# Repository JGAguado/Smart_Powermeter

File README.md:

[![Documentation Status][documentation-shield]][documentation]
[![GitHub Release][releases-shield]][releases]
[![License][license-shield]](LICENSE)

[![Project Maintenance][maintenance-shield]][maintenance]
[![BuyMeCoffee][buymecoffee-shield]][buymecoffee]

# Smart Powermeter
The Smart Powermeter is powered by a ESP32-S2, allowing the measurement up to 6 CT clamps for reading electric current and real-time display on an 2.9" e-paper display.

Additionally, the 3rd version adds support to voltage measurement with up to 3 voltage measurement channels and independent adjustable gains. 

## Project tree

<li><a href="./Design/">Design</a></li>
<li><a href="./Documentation/">Documentation</a></li>

<li><a href="./README.md">README.md</a></li>

[documentation-shield]: https://readthedocs.org/projects/smart-powermeter/badge/?version=latest&style=for-the-badge
[documentation]: https://smart-powermeter.readthedocs.io/en/latest/

[releases-shield]: https://img.shields.io/github/release/JGAguado/Smart_Powermeter.svg?style=for-the-badge
[releases]: https://github.com/JGAguado/Smart_Powermeter/releases

[license-shield]: https://img.shields.io/badge/License-CC%20BY--NC--SA%204.0-lightgrey.svg?style=for-the-badge

[maintenance-shield]: https://img.shields.io/badge/maintainer-J.%20G.%20Aguado-blue.svg?style=for-the-badge
[maintenance]: https://github.com/JGAguado

[buymecoffee-shield]: https://img.shields.io/badge/buy%20me%20a%20coffee-support-yellow.svg?style=for-the-badge
[buymecoffee]: https://www.buymeacoffee.com/J.G.Aguado

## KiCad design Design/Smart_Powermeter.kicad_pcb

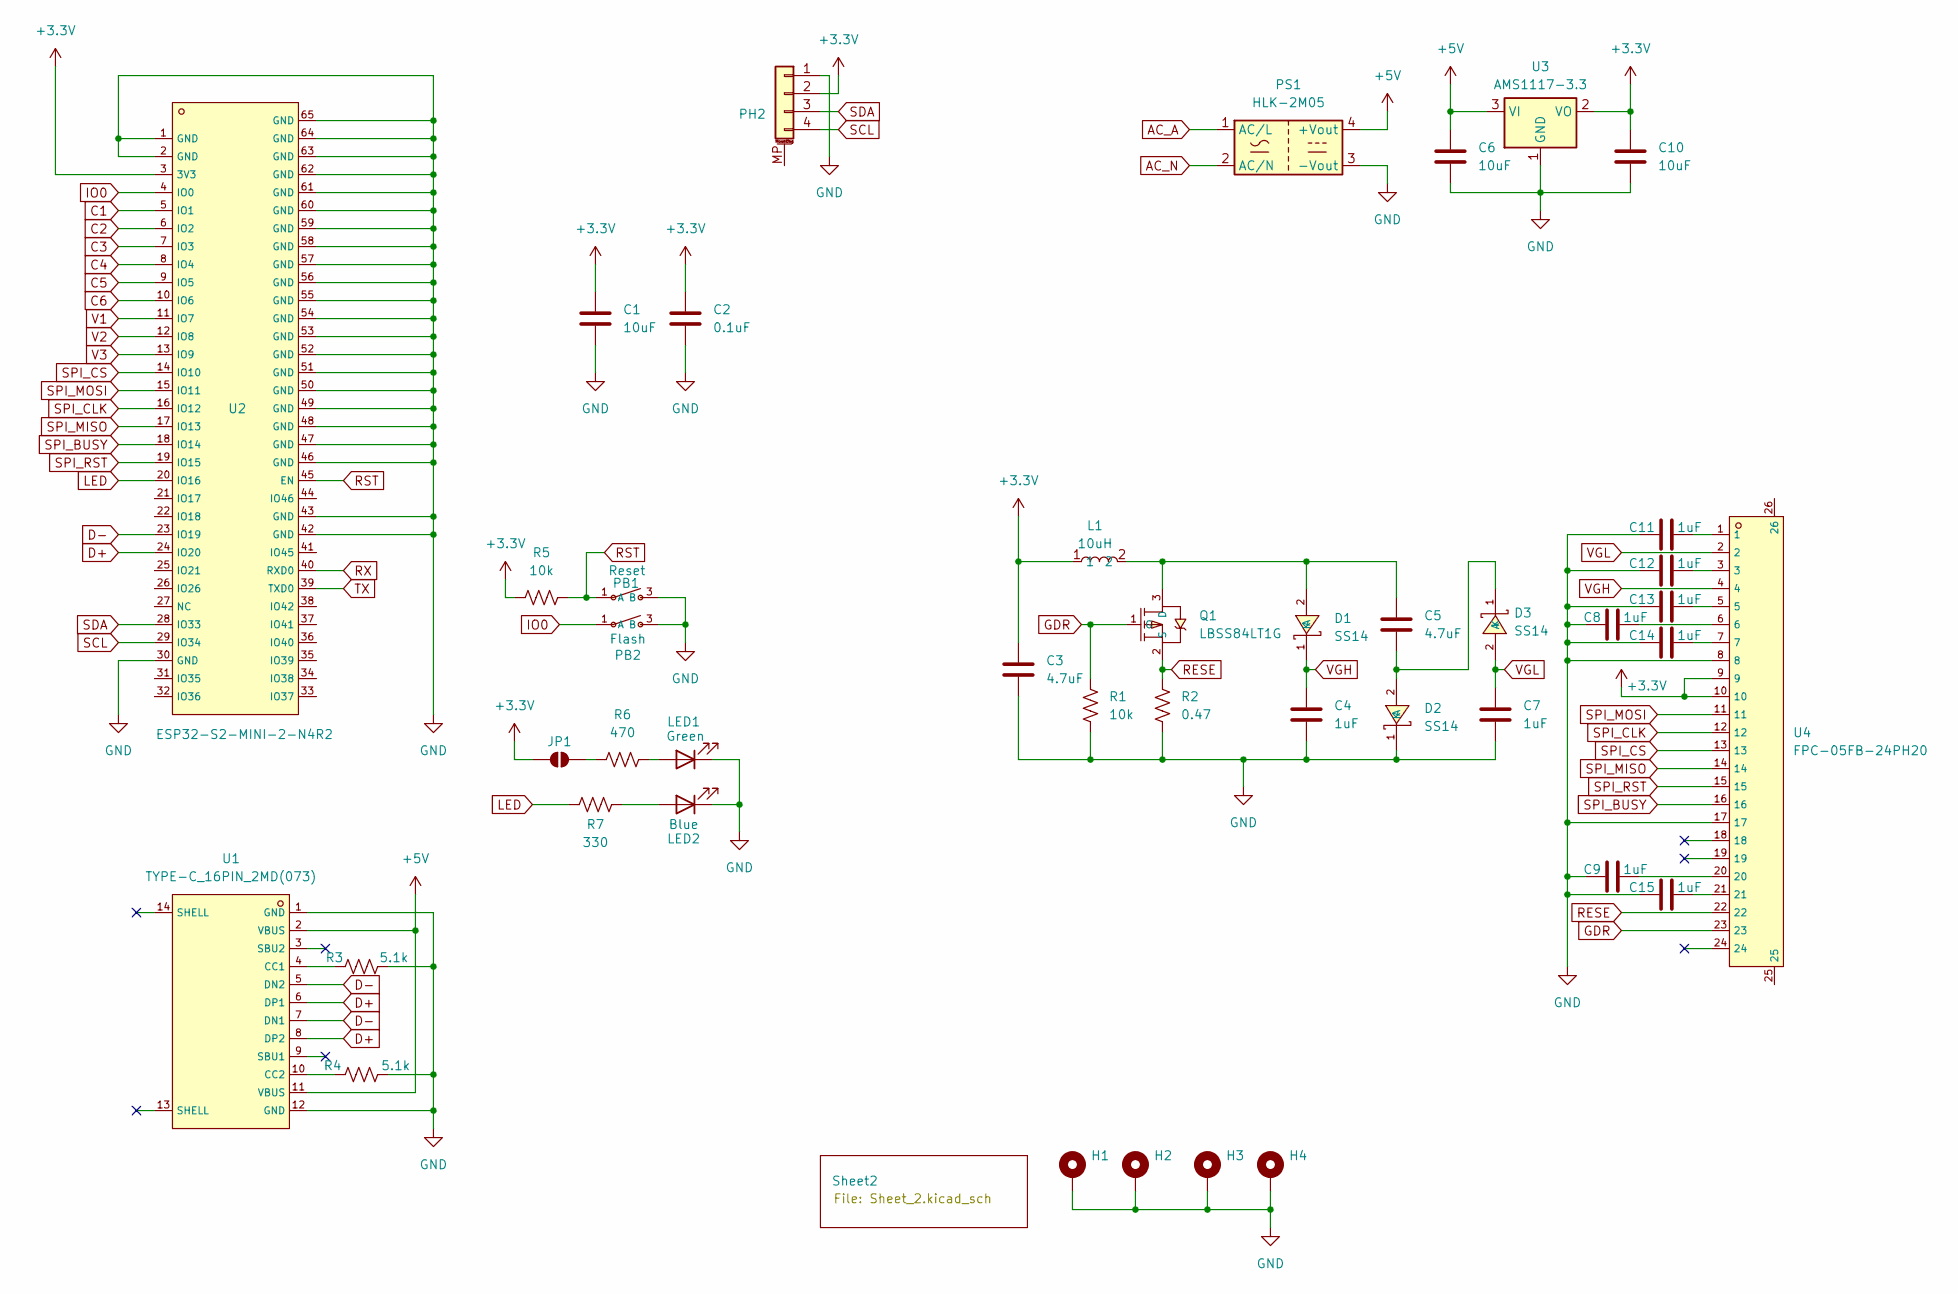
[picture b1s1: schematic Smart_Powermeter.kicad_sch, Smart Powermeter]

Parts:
C1, C6, C10: 10uF; C_0603_1608Metric
C2: 0.1uF; C_0603_1608Metric
C3, C5: 4.7uF; C_0603_1608Metric
C4, C7, C8, C9, C11, C12, C13, C14, C15: 1uF; C_0603_1608Metric
D1, D2, D3: SS14; SMA_L4.2-W2.6-LS5.3-RD; LCSC C2480
H1, H2, H3, H4: MountingHole_Pad; MountingHole_3.5mm_Pad_Via
JP1: SolderJumper_2_Bridged; SolderJumper-2_P1.3mm_Open_RoundedPad1.0x1.5mm
L1: 10uH; IND-SMD_L4.0-W4.0; LCSC C340393
LED1: Green; LED_0603_1608Metric
LED2: Blue; LED_0603_1608Metric
PB1: Reset; SW-SMD_4P-L4.5-W4.5-P3.00-LS6.8; LCSC C5342982
PB2: Flash; SW-SMD_4P-L4.5-W4.5-P3.00-LS6.8; LCSC C5342982
PH2: Conn_01x04_MountingPin; PinHeader_1x04_P2.54mm_Vertical
PS1: HLK-2M05; Converter_ACDC_Hi-Link_HLK-2Mxx
Q1: LBSS84LT1G; SOT-23_L2.9-W1.3-P1.90-LS2.4-BR; LCSC C8492
R1, R5: 10k; R_0603_1608Metric
R2: 0.47; R_0603_1608Metric
R3, R4: 5.1k; R_0603_1608Metric
R6: 470; R_0603_1608Metric
R7: 330; R_0603_1608Metric
U1: TYPE-C_16PIN_2MD(073); USB-C-SMD_TYPE-C-6PIN-2MD-073; LCSC C2765186
U2: ESP32-S2-MINI-2-N4R2; WIFI-SMD_ESP32-MINI-1-N4; LCSC C3013908
U3: AMS1117-3.3; SOT-223-3_TabPin2
U4: FPC-05FB-24PH20; FPC-SMD_24P-P0.50_FPC-05FB-24PH20; LCSC C2856831

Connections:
+3.3V: C1.1, C2.1, C3.1, C10.1, JP1.1 (A), L1.1, PH2.2, R5.1, U2.3 (3V3), U3.2 (VO), U4.9, U4.10; also elsewhere on the board
+5V: C6.1, PS1.4 (+Vout), U1.2 (VBUS), U1.11 (VBUS), U3.3 (VI); also elsewhere on the board
AC_A: PS1.1 (AC/L); also elsewhere on the board
AC_N: PS1.2 (AC/N); also elsewhere on the board
C1: U2.5 (IO1); also elsewhere on the board
C2: U2.6 (IO2); also elsewhere on the board
C3: U2.7 (IO3); also elsewhere on the board
C4: U2.8 (IO4); also elsewhere on the board
C5: U2.9 (IO5); also elsewhere on the board
C6: U2.10 (IO6); also elsewhere on the board
D+: U1.6 (DP1), U1.8 (DP2), U2.24 (IO20)
D-: U1.5 (DN2), U1.7 (DN1), U2.23 (IO19)
GDR: Q1.1 (G), R1.1, U4.23
GND: C1.2, C2.2, C3.2, C4.2, C6.2, C7.2, C8.1, C9.1, C10.2, C11.1, C12.1, C13.1, C14.1, C15.1, D2.1 (K), H1.1, H2.1, H3.1, H4.1, LED1.1 (K), LED2.1 (K), PB1.3 (B), PB2.3 (B), PH2.1, PS1.3 (-Vout), R1.2, R2.2, R3.2, R4.2, U1.1 (GND), U1.12 (GND), U2.1 (GND), U2.2 (GND), U2.30 (GND), U2.42 (GND), U2.43 (GND), U2.46 (GND), U2.47 (GND), U2.48 (GND), U2.49 (GND), U2.50 (GND), U2.51 (GND), U2.52 (GND), U2.53 (GND), U2.54 (GND), U2.55 (GND), U2.56 (GND), U2.57 (GND), U2.58 (GND), U2.59 (GND), U2.60 (GND), U2.61 (GND), U2.62 (GND), U2.63 (GND), U2.64 (GND), U2.65 (GND), U3.1 (GND), U4.8, U4.17; also elsewhere on the board
IO0: PB2.1 (A), U2.4 (IO0)
LED: R7.1, U2.20 (IO16)
unnamed: C8.2, U4.6
unnamed: C9.2, U4.20
unnamed: C11.2, U4.1
unnamed: C12.2, U4.3
unnamed: C13.2, U4.5
unnamed: C14.2, U4.7
unnamed: C15.2, U4.21
unnamed: C5.1, D1.2 (A), L1.2, Q1.3 (D)
unnamed: C5.2, D2.2 (A), D3.1 (K)
unnamed: JP1.2 (B), R6.1
unnamed: LED1.2 (A), R6.2
unnamed: LED2.2 (A), R7.2
unnamed: R3.1, U1.4 (CC1)
unnamed: R4.1, U1.10 (CC2)
RESE: Q1.2 (S), R2.1, U4.22
RST: PB1.1 (A), R5.2, U2.45 (EN)
RX: U2.40 (RXD0)
SCL: PH2.4, U2.29 (IO34)
SDA: PH2.3, U2.28 (IO33)
SPI_BUSY: U2.18 (IO14), U4.16
SPI_CLK: U2.16 (IO12), U4.12
SPI_CS: U2.14 (IO10), U4.13
SPI_MISO: U2.17 (IO13), U4.14
SPI_MOSI: U2.15 (IO11), U4.11
SPI_RST: U2.19 (IO15), U4.15
TX: U2.39 (TXD0)
V1: U2.11 (IO7); also elsewhere on the board
V2: U2.12 (IO8); also elsewhere on the board
V3: U2.13 (IO9); also elsewhere on the board
VGH: C4.1, D1.1 (K), U4.4
VGL: C7.1, D3.2 (A), U4.2

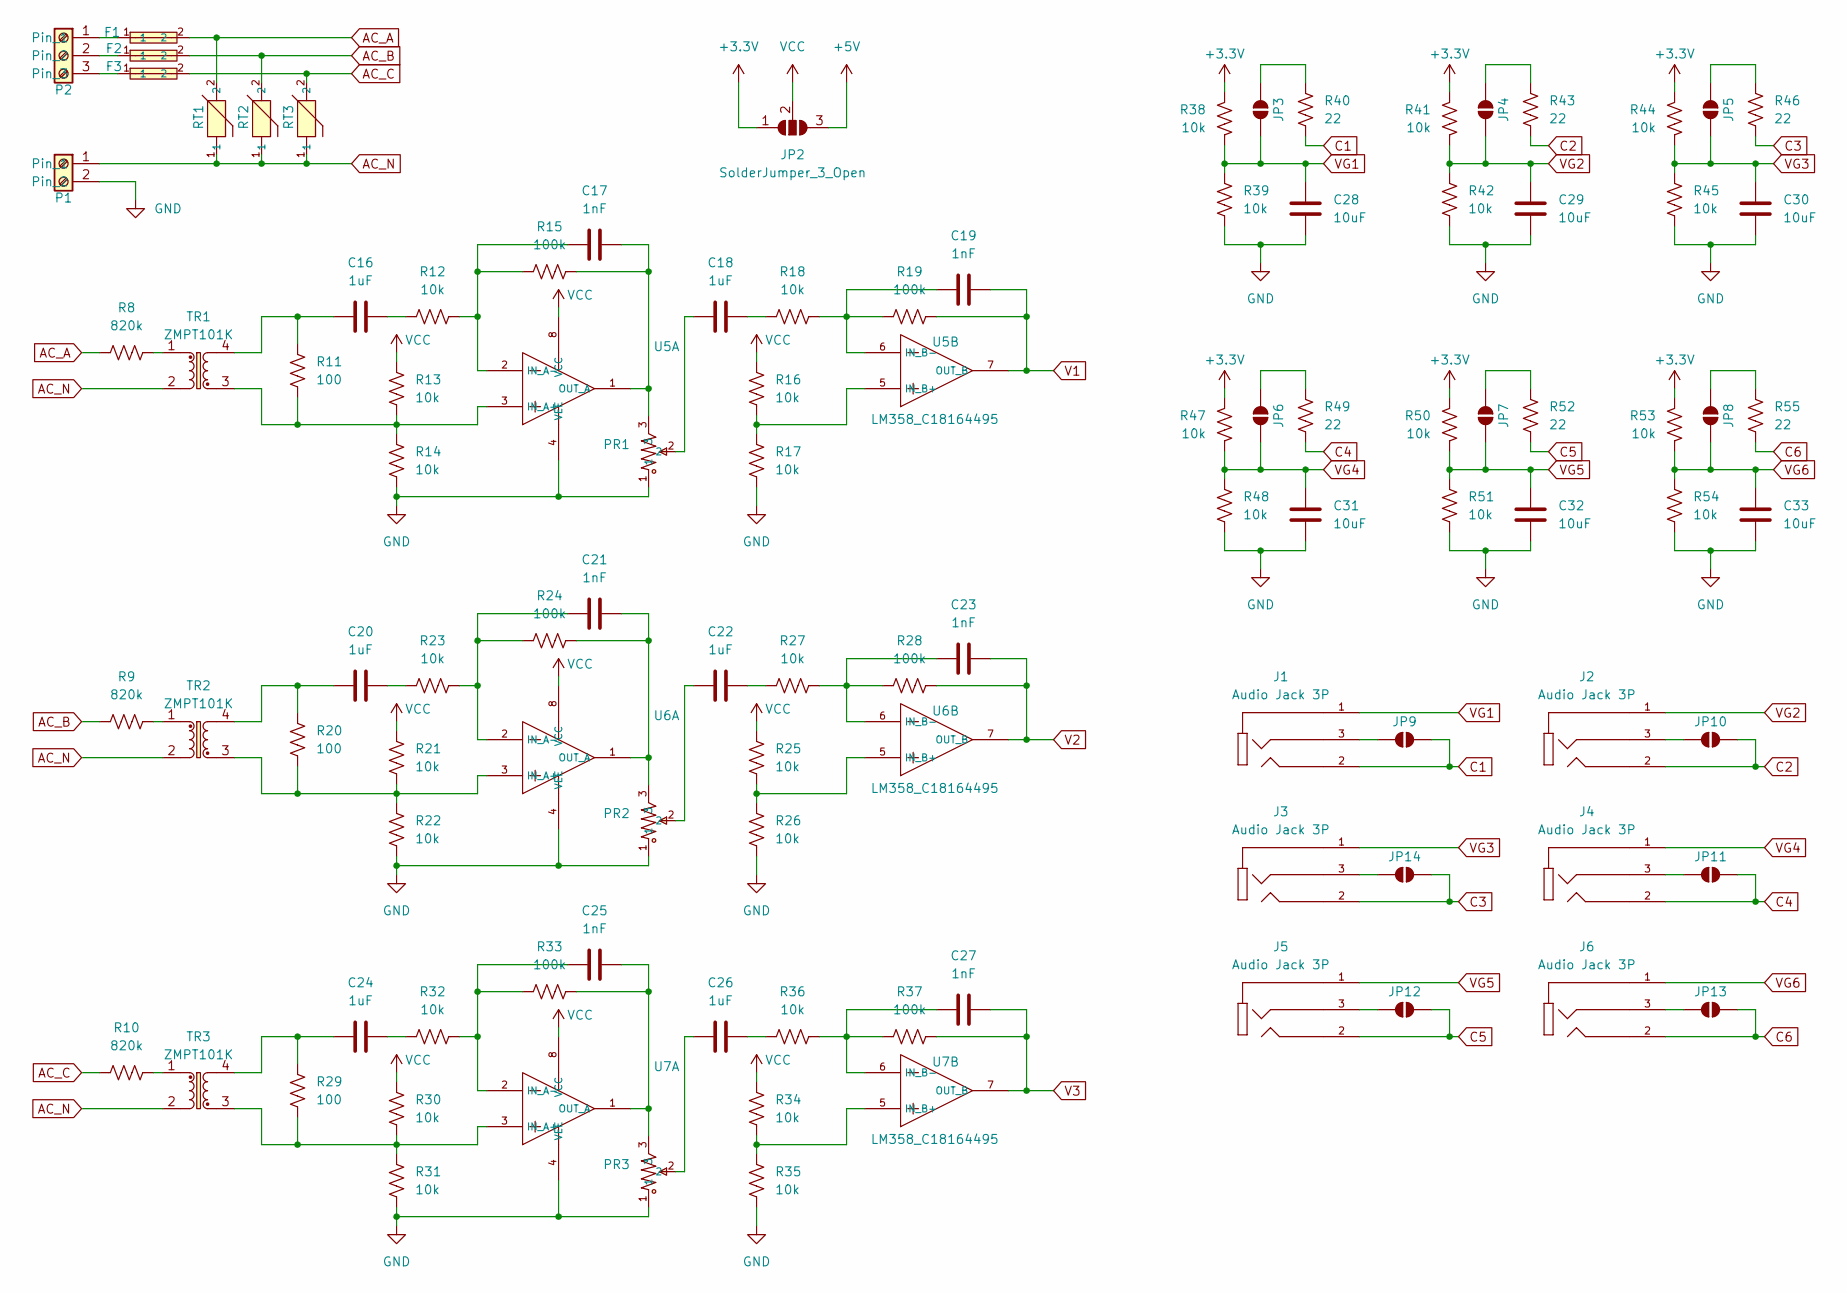
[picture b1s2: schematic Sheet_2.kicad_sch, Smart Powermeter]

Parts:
C16, C18, C20, C22, C24, C26: 1uF; C_0603_1608Metric
C17, C19, C21, C23, C25, C27: 1nF; C_0603_1608Metric
C28, C29, C30, C31, C32, C33: 10uF; C_0603_1608Metric
F1, F2, F3: MST1A250V; FUSE-TH_L8.4-W4.3-P5.08-D0.7; LCSC C340909
J1, J2, J3, J4, J5, J6: Audio Jack 3P; PJ-320B; PARTREV 1.05
JP2: SolderJumper_3_Open; SolderJumper-3_P1.3mm_Bridged12_RoundedPad1.0x1.5mm_NumberL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
JP3, JP4, JP5, JP6, JP7, JP8, JP9, JP10, JP11, JP12, JP13, JP14: SolderJumper_2_Bridged; SolderJumper-2_P1.3mm_Open_RoundedPad1.0x1.5mm
P1: WJ300V-5_0-2P; CONN-TH_2P-P5.00_WJ300V-5.00-2P; LCSC C8385
P2: WJ300V-5_0-3P; CONN-TH_3P-P5.00_WJ300V-5.00-3P; LCSC C8467
PR1, PR2, PR3: 3296W-1-103; RES-ADJ-TH_3P-L10.0-W10.0-P2.50-L; LCSC C118954
R8, R9, R10: 820k; R_1206_3216Metric
R11, R20, R29: 100; R_0603_1608Metric
R12, R13, R14, R16, R17, R18, R21, R22, R23, R25, R26, R27, R30, R31, R32, R34, R35, R36, R38, R39, R41, R42, R44, R45, R47, R48, R50, R51, R53, R54: 10k; R_0603_1608Metric
R15, R19, R24, R28, R33, R37: 100k; R_0603_1608Metric
R40, R43, R46, R49, R52, R55: 22; R_0603_1608Metric
RT1, RT2, RT3: 10D561K_C338652; RES-TH_L13.0-W6.7-P7.50-D0.7-S5.30; LCSC C338652
TR1, TR2, TR3: ZMPT101K; XFMR-TH_ZMPT101K; LCSC C3034722
U5, U6, U7: LM358_C18164495; SOIC-8_L4.9-W3.9-P1.27-LS6.0-BL; LCSC C18164495

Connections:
+3.3V: JP2.1 (A), R38.2, R41.2, R44.2, R47.2, R50.2, R53.2; also elsewhere on the board
+5V: JP2.3 (B); also elsewhere on the board
AC_A: F1.2, R8.1, RT1.2; also elsewhere on the board
AC_B: F2.2, R9.1, RT2.2
AC_C: F3.2, R10.1, RT3.2
AC_N: P1.1, RT1.1, RT2.1, RT3.1, TR1.2, TR2.2, TR3.2; also elsewhere on the board
C1: J1.2, JP9.1 (A), R40.1; also elsewhere on the board
C2: J2.2, JP10.1 (A), R43.1; also elsewhere on the board
C3: J3.2, JP14.1 (A), R46.1; also elsewhere on the board
C4: J4.2, JP11.1 (A), R49.1; also elsewhere on the board
C5: J5.2, JP12.1 (A), R52.1; also elsewhere on the board
C6: J6.2, JP13.1 (A), R55.1; also elsewhere on the board
GND: C28.2, C29.2, C30.2, C31.2, C32.2, C33.2, P1.2, PR1.1, PR2.1, PR3.1, R14.1, R17.1, R22.1, R26.1, R31.1, R35.1, R39.1, R42.1, R45.1, R48.1, R51.1, R54.1, U5.4 (VEE), U6.4 (VEE), U7.4 (VEE); also elsewhere on the board
unnamed: C16.1, R12.1
unnamed: C16.2, R11.1, TR1.4
unnamed: C18.1, R18.1
unnamed: C18.2, PR1.2
unnamed: C20.1, R23.1
unnamed: C20.2, R20.1, TR2.4
unnamed: C22.1, R27.1
unnamed: C22.2, PR2.2
unnamed: C24.1, R32.1
unnamed: C24.2, R29.1, TR3.4
unnamed: C26.1, R36.1
unnamed: C26.2, PR3.2
unnamed: JP3.2 (B), R40.2
unnamed: JP4.2 (B), R43.2
unnamed: JP5.2 (B), R46.2
unnamed: JP6.2 (B), R49.2
unnamed: JP7.2 (B), R52.2
unnamed: JP8.2 (B), R55.2
unnamed: J1.3, JP9.2 (B)
unnamed: J2.3, JP10.2 (B)
unnamed: J4.3, JP11.2 (B)
unnamed: J5.3, JP12.2 (B)
unnamed: J6.3, JP13.2 (B)
unnamed: J3.3, JP14.2 (B)
unnamed: F1.1, P2.1
unnamed: F2.1, P2.2
unnamed: F3.1, P2.3
unnamed: R8.2, TR1.1
unnamed: R9.2, TR2.1
unnamed: R10.2, TR3.1
unnamed: R11.2, R13.1, R14.2, TR1.3, U5.3 (IN_A+)
unnamed: C17.2, R12.2, R15.1, U5.2 (IN_A-)
unnamed: C17.1, PR1.3, R15.2, U5.1 (OUT_A)
unnamed: R16.1, R17.2, U5.5 (IN_B+)
unnamed: C19.2, R18.2, R19.1, U5.6 (IN_B-)
unnamed: R20.2, R21.1, R22.2, TR2.3, U6.3 (IN_A+)
unnamed: C21.2, R23.2, R24.1, U6.2 (IN_A-)
unnamed: C21.1, PR2.3, R24.2, U6.1 (OUT_A)
unnamed: R25.1, R26.2, U6.5 (IN_B+)
unnamed: C23.2, R27.2, R28.1, U6.6 (IN_B-)
unnamed: R29.2, R30.1, R31.2, TR3.3, U7.3 (IN_A+)
unnamed: C25.2, R32.2, R33.1, U7.2 (IN_A-)
unnamed: C25.1, PR3.3, R33.2, U7.1 (OUT_A)
unnamed: R34.1, R35.2, U7.5 (IN_B+)
unnamed: C27.2, R36.2, R37.1, U7.6 (IN_B-)
V1: C19.1, R19.2, U5.7 (OUT_B); also elsewhere on the board
V2: C23.1, R28.2, U6.7 (OUT_B); also elsewhere on the board
V3: C27.1, R37.2, U7.7 (OUT_B); also elsewhere on the board
VCC: JP2.2 (C), R13.2, R16.2, R21.2, R25.2, R30.2, R34.2, U5.8 (VCC), U6.8 (VCC), U7.8 (VCC)
VG1: C28.1, J1.1, JP3.1 (A), R38.1, R39.2
VG2: C29.1, J2.1, JP4.1 (A), R41.1, R42.2
VG3: C30.1, J3.1, JP5.1 (A), R44.1, R45.2
VG4: C31.1, J4.1, JP6.1 (A), R47.1, R48.2
VG5: C32.1, J5.1, JP7.1 (A), R50.1, R51.2
VG6: C33.1, J6.1, JP8.1 (A), R53.1, R54.2

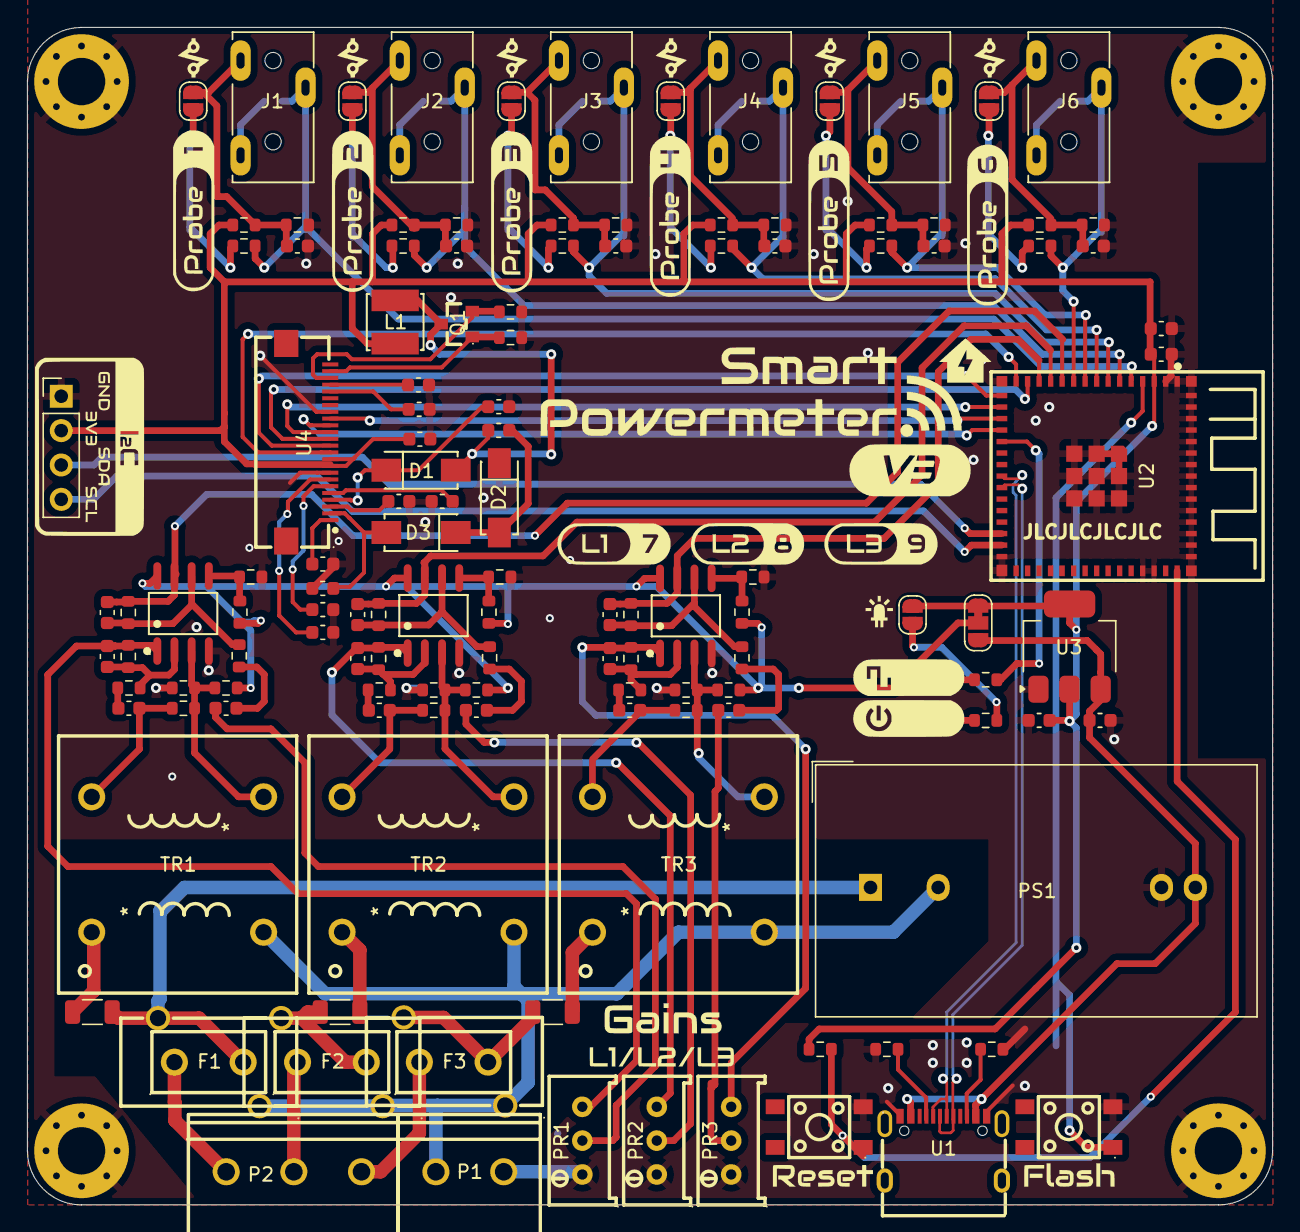
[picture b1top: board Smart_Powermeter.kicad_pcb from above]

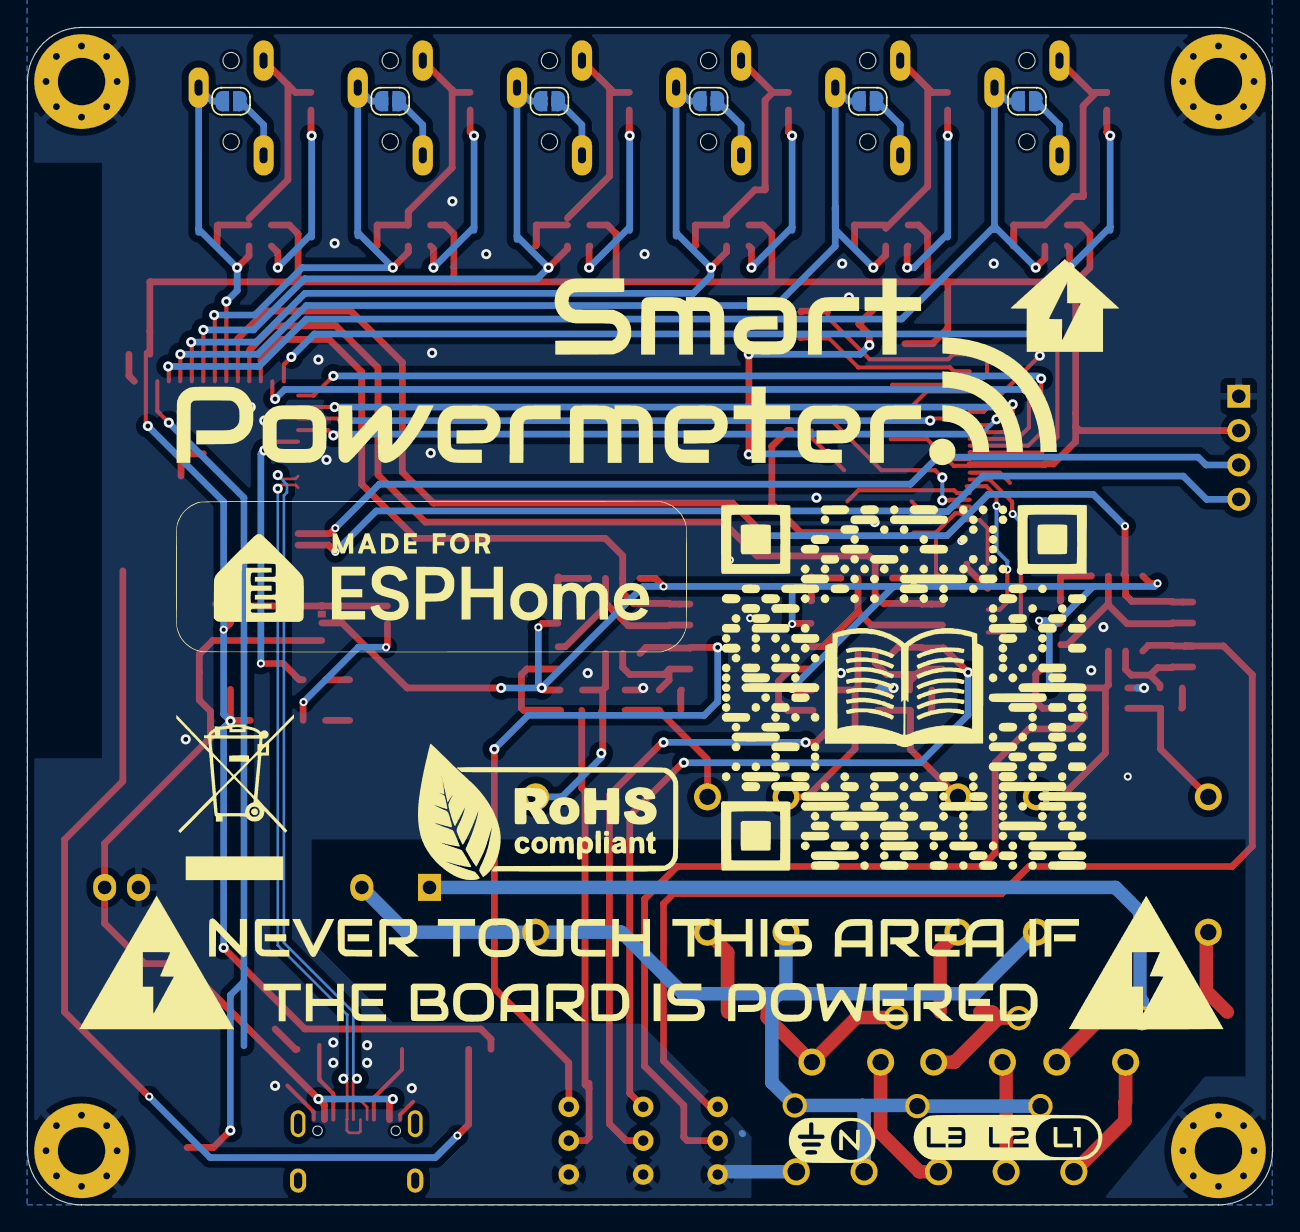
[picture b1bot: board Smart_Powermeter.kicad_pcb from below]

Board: 2 copper layers, 92.0 x 87.0 mm, 144 parts (6 on the bottom side), 99 nets.

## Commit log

2022-04-13 Added silkscreen design
2022-04-13 Added design files
2022-04-13 Added Documentation
2022-04-13 Updated silkscreen files
2022-04-13 Updated design files fixing Release 1 bugs
2022-04-13 Updated documentation
2022-05-11 Updated documentation with added Datasheet
2022-05-29 Resize dimensions to fit in the 92x87 enclosure
2023-04-19 Added design files of V2
2023-04-19 Added Documentation V3
2023-04-19 docs
2023-04-19 README.md
2023-07-02 updated configuration.yaml
2023-11-14 Updated design files
2024-01-31 fixed the missing "0" on the docs
2024-03-19 First draft for the Pro version
2024-04-03 Updated design files and silkscreen
2024-04-03 Added alternative configuration_1.yaml with: - Web server - MQTT - Input coefficients for linear calibration "a*x + b"
2024-04-19 Documentation
2024-04-22 Removed secrets from configuration.yaml
2024-04-22 removed custom files from configuration.yaml
2024-04-22 Removed custom components from configuration.yaml
2024-05-03 Readme
2024-06-12 Smart Powermeter Pro with V/I measurements directly on the ESP32-S2
2024-06-14 11dB -> 12dB
2024-06-20 fix typos
2024-07-10 Former Eagle files moved to Eagle
2024-07-10 Added KiCad files with a first draft for the V3R1
2024-08-01 First draft V3R1
2024-08-06 Cleared path around antenna and removed Serial port
2025-03-03 Update configuration.yaml to work with >= ESPHome 2025.2.0
    https://esphome.io/changelog/2025.2.0.html#image-components
    "the type configuration variable is now mandatory"
2025-05-04 Add GA support
